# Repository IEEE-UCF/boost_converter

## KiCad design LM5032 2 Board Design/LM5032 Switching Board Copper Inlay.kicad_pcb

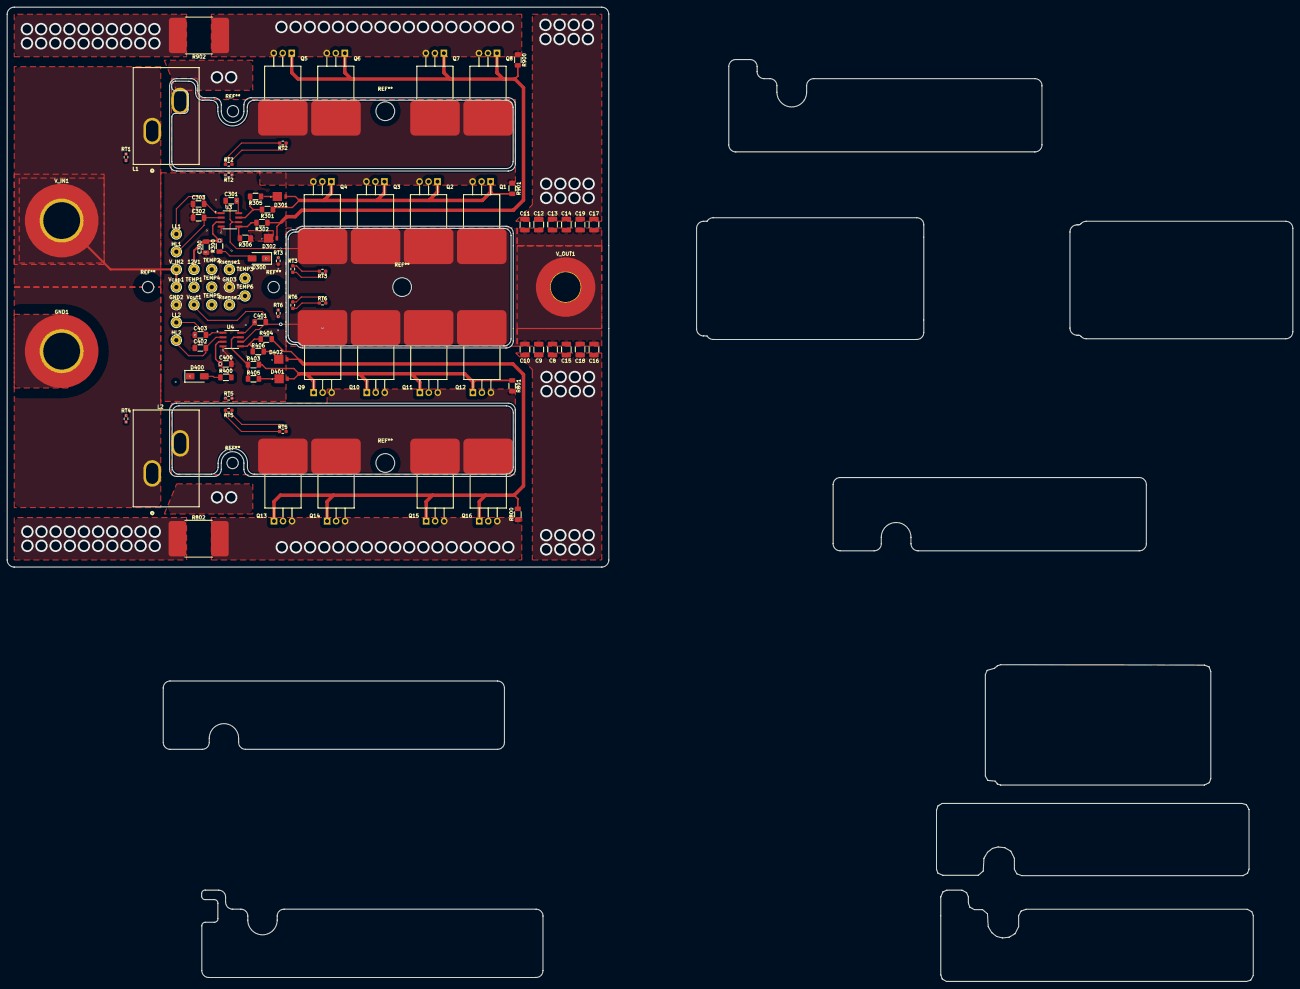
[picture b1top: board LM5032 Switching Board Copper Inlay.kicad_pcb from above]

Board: 4 copper layers, 170.0 x 158.2 mm, 97 parts (0 on the bottom side), 34 nets.

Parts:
12V1: MountingHole_Pad; TestPoint_THTPad_D2.5mm_Drill1.2mm
C8, C9, C10, C11, C12, C13, C14, C15: 10uF; C_1210_3225Metric_Pad1.33x2.70mm_HandSolder
C16, C17, C18, C19: 0.1uF; C_1210_3225Metric_Pad1.33x2.70mm_HandSolder
C300, C400: 22uF; C_1206_3216Metric_Pad1.33x1.80mm_HandSolder
C301, C401: 2.2uF; C_1206_3216Metric_Pad1.33x1.80mm_HandSolder
C302, C303, C402, C403: 33pF; C_1206_3216Metric_Pad1.33x1.80mm_HandSolder
D300, D400: BYG20J-E3/TR; D_SMA
D301, D302, D401, D402: MBRM130LT1G
GND1: MountingHole_Pad; MountingHole_8.4mm_M8_Pad_TopBottom
GND2, GND3: MountingHole_Pad; TestPoint_THTPad_D2.5mm_Drill1.2mm
HL1, HL2: MountingHole_Pad; TestPoint_THTPad_D2.5mm_Drill1.2mm
L1, L2: 470nH; EDITED-IND_IHDM1107BBEVR47M20_VIS
LL1, LL2: MountingHole_Pad; TestPoint_THTPad_D2.5mm_Drill1.2mm
Q1, Q2, Q3, Q4, Q5, Q6, Q7, Q8, Q9, Q10, Q11, Q12, Q13, Q14, Q15, Q16: NMOS; TO-220-3_Horizontal_TabDown no hole
R300, R400: 49.9; R_1206_3216Metric_Pad1.30x1.75mm_HandSolder
R301, R302, R403, R404: 3.3; R_1206_3216Metric_Pad1.30x1.75mm_HandSolder
R305, R306, R405, R406: 2.2; R_1206_3216Metric_Pad1.30x1.75mm_HandSolder
R800, R801, R900, R901: 1k; R_1206_3216Metric_Pad1.30x1.75mm_HandSolder
R802, R902: 0.0001; PSR500HTQFB0L10
RT1, RT2, RT2#2, RT2#3, RT3, RT3#2, RT3#3, RT4, RT5, RT5#2, RT5#3, RT6, RT6#2, RT6#3: 36.5k; R_0603_1608Metric_Pad0.98x0.95mm_HandSolder
Rsense1, Rsense2: MountingHole_Pad; TestPoint_THTPad_D2.5mm_Drill1.2mm
TEMP1, TEMP2, TEMP3, TEMP4, TEMP5, TEMP6: MountingHole_Pad; TestPoint_THTPad_D2.5mm_Drill1.2mm
U3, U4: UCC27712DR; SOIC127P599X175-8N
V_IN1: MountingHole_Pad; MountingHole_8.4mm_M8_Pad_TopBottom
V_IN2: MountingHole_Pad; TestPoint_THTPad_D2.5mm_Drill1.2mm
V_OUT1: MountingHole_Pad; MountingHole_8.4mm_M8_Pad_TopBottom
Vcap1: MountingHole_Pad; TestPoint_THTPad_D2.5mm_Drill1.2mm
Vout1: MountingHole_Pad; TestPoint_THTPad_D2.5mm_Drill1.2mm

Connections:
/12V: 12V1.1, C300.2, C400.2, R300.2, R400.2, U3.3 (VDD), U4.3 (VDD)
/HL1: C302.2, HL1.1, U3.2 (HL)
/HL2: C402.2, HL2.1, U4.2 (HL)
/HO1: D301.2 (A), Q1.2 (G), Q2.2 (G), Q3.2 (G), Q4.2 (G), R301.1, R901.2
/HO2: D401.2 (A), Q9.2 (G), Q10.2 (G), Q11.2 (G), Q12.2 (G), R403.1, R801.2
/LL1: C303.2, LL1.1, U3.1 (LL)
/LL2: C403.2, LL2.1, U4.1 (LL)
/LO1: D302.2 (A), Q5.2 (G), Q6.2 (G), Q7.2 (G), Q8.2 (G), R302.1, R900.2
/LO2: D402.2 (A), Q13.2 (G), Q14.2 (G), Q15.2 (G), Q16.2 (G), R404.1, R800.2
/Rsense1: Q5.3 (S), Q6.3 (S), Q7.3 (S), Q8.3 (S), R900.1, R902.1, Rsense1.1
/Rsense2: Q13.3 (S), Q14.3 (S), Q15.3 (S), Q16.3 (S), R800.1, R802.1, Rsense2.1
GND: C8.2, C9.2, C10.2, C11.2, C12.2, C13.2, C14.2, C15.2, C16.2, C17.2, C18.2, C19.2, C300.1, C302.1, C303.1, C400.1, C402.1, C403.1, GND1.1, GND2.1, GND3.1, R802.2, R902.2, RT1.1, RT2#3.1, RT3#2.2, RT4.2, RT5#3.2, RT6#2.2, U3.4 (COM), U4.4 (COM)
unnamed: D300.2 (A), R300.1
unnamed: C301.1, D300.1 (K), U3.8 (HB)
unnamed: D301.1 (K), R305.1
unnamed: D302.1 (K), R306.1
unnamed: D400.2 (A), R400.1
unnamed: C401.1, D400.1 (K), U4.8 (HB)
unnamed: D401.1 (K), R405.1
unnamed: D402.1 (K), R406.1
unnamed: L1.2, Q1.3 (S), Q2.3 (S), Q3.3 (S), Q4.3 (S), Q5.1 (D), Q6.1 (D), Q7.1 (D), Q8.1 (D), R901.1
unnamed: L2.2, Q9.3 (S), Q10.3 (S), Q11.3 (S), Q12.3 (S), Q13.1 (D), Q14.1 (D), Q15.1 (D), Q16.1 (D), R801.1
unnamed: RT1.2, TEMP1.1
unnamed: RT2#3.2, TEMP2.1
unnamed: RT3#2.1, TEMP3.1
unnamed: RT4.1, TEMP4.1
unnamed: RT5#3.1, TEMP5.1
unnamed: RT6#2.1, TEMP6.1
unnamed: R301.2, R305.2, U3.7 (HO)
unnamed: R302.2, R306.2, U3.5 (LO)
unnamed: R403.2, R405.2, U4.7 (HO)
unnamed: R404.2, R406.2, U4.5 (LO)
Vin: L1.1, L2.1, V_IN1.1, V_IN2.1, Vcap1.1
Vout: C8.1, C9.1, C10.1, C11.1, C12.1, C13.1, C14.1, C15.1, C16.1, C17.1, C18.1, C19.1, C301.2, C401.2, Q1.1 (D), Q2.1 (D), Q3.1 (D), Q4.1 (D), Q9.1 (D), Q10.1 (D), Q11.1 (D), Q12.1 (D), U3.6 (HS), U4.6 (HS), V_OUT1.1, Vout1.1

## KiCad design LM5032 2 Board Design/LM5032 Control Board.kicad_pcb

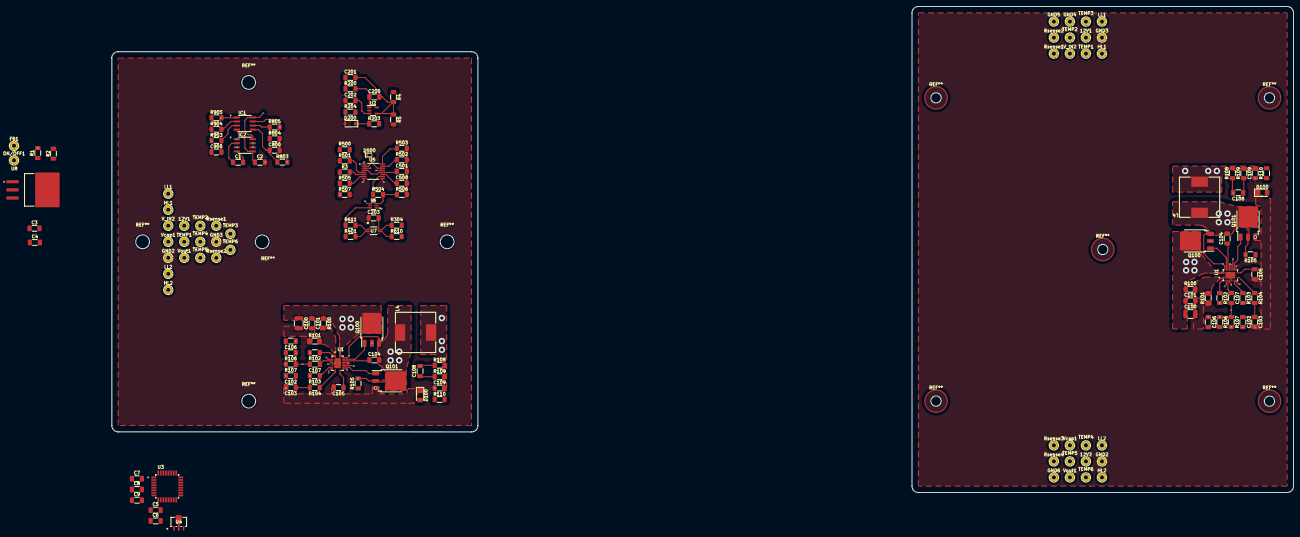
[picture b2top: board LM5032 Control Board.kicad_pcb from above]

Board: 4 copper layers, 368.6 x 151.6 mm, 150 parts (0 on the bottom side), 60 nets.

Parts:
12V1, 12V1#2, 12V2: MountingHole_Pad; TestPoint_THTPad_D2.5mm_Drill1.2mm
C1, C2, C4, C5: 1uF; C_1206_3216Metric_Pad1.33x1.80mm_HandSolder
C3: 4.7uF; C_1206_3216Metric_Pad1.33x1.80mm_HandSolder
C6: 10uF; C_1206_3216Metric_Pad1.33x1.80mm_HandSolder
C7, C8, C9, C201, C202, C203, C500, C501: 0.1uF; C_1206_3216Metric_Pad1.33x1.80mm_HandSolder
C100, C100#2: 10uF; C_1210_3225Metric_Pad1.33x2.70mm_HandSolder
C101, C101#2, C104, C104#2, C105, C105#2: 100nF; C_1206_3216Metric_Pad1.33x1.80mm_HandSolder
C102, C102#2: 56nF; C_1206_3216Metric_Pad1.33x1.80mm_HandSolder
C103, C103#2: 2.2uF; C_1206_3216Metric_Pad1.33x1.80mm_HandSolder
C106, C106#2: 8.2nF; C_1206_3216Metric_Pad1.33x1.80mm_HandSolder
C107, C107#2, C200: 470pF; C_1206_3216Metric_Pad1.33x1.80mm_HandSolder
C108, C108#2: 820pF; C_1206_3216Metric_Pad1.33x1.80mm_HandSolder
C109, C109#2: 22uF; C_1206_3216Metric_Pad1.33x1.80mm_HandSolder
C800, C900: 100pF; C_1206_3216Metric_Pad1.33x1.80mm_HandSolder
D100, D100#2: LED; LED_1206_3216Metric_Pad1.42x1.75mm_HandSolder
D200: 2.0V; D_SOD-123
D500: CMOD4448 TR PBFREE; D_SOD-523
FB1: MountingHole_Pad; TestPoint_THTPad_D2.5mm_Drill1.2mm
GND2, GND2#2, GND3, GND3#2, GND4, GND5, GND6: MountingHole_Pad; TestPoint_THTPad_D2.5mm_Drill1.2mm
HL1, HL1#2, HL2, HL2#2: MountingHole_Pad; TestPoint_THTPad_D2.5mm_Drill1.2mm
IC1: AD8092ARZ; SOIC127P600X175-8N
IC2: MAX1681ESA+; SOIC127P600X175-8N
L4, L4#2: 22uH; IND_MSS1210_COC
LL1, LL1#2, LL2, LL2#2: MountingHole_Pad; TestPoint_THTPad_D2.5mm_Drill1.2mm
ON/OFF1: MountingHole_Pad; TestPoint_THTPad_D2.5mm_Drill1.2mm
Q100, Q100#2, Q101, Q101#2: DMT10H009LK3-13; TO-252-3_TabPin2 modded
R1: 5.36k (47k); R_1206_3216Metric_Pad1.30x1.75mm_HandSolder
R2, R3, R110, R110#2, R610, R611: 1k; R_1206_3216Metric_Pad1.30x1.75mm_HandSolder
R4: 36.5k; R_1206_3216Metric_Pad1.30x1.75mm_HandSolder
R5: 1.37k; R_1206_3216Metric_Pad1.30x1.75mm_HandSolder
R100, R100#2: 62.0k; R_1206_3216Metric_Pad1.30x1.75mm_HandSolder
R101, R101#2: 4.99k; R_1206_3216Metric_Pad1.30x1.75mm_HandSolder
R102, R102#2: 39.2k; R_1206_3216Metric_Pad1.30x1.75mm_HandSolder
R103, R103#2, R104, R104#2: 20k; R_1206_3216Metric_Pad1.30x1.75mm_HandSolder
R105, R105#2: 866; R_1206_3216Metric_Pad1.30x1.75mm_HandSolder
R106, R106#2: 2.87k; R_1206_3216Metric_Pad1.30x1.75mm_HandSolder
R107, R107#2: 1.27k; R_1206_3216Metric_Pad1.30x1.75mm_HandSolder
R108, R108#2: 18k; R_1206_3216Metric_Pad1.30x1.75mm_HandSolder
R109, R109#2: 24.9; R_1206_3216Metric_Pad1.30x1.75mm_HandSolder
R200: 30.1k; R_1206_3216Metric_Pad1.30x1.75mm_HandSolder
R203, R204: 2.0k; R_1206_3216Metric_Pad1.30x1.75mm_HandSolder
R304, R401, R504, R505, R506, R507: 150; R_1206_3216Metric_Pad1.30x1.75mm_HandSolder
R500: 36.5k (35.7k); R_1206_3216Metric_Pad1.30x1.75mm_HandSolder
R501: 1.1k; R_1206_3216Metric_Pad1.30x1.75mm_HandSolder
R502, R503: 34.1k; R_1206_3216Metric_Pad1.30x1.75mm_HandSolder
R803, R903: 300; R_1206_3216Metric_Pad1.30x1.75mm_HandSolder
R804, R904: 10k; R_1206_3216Metric_Pad1.30x1.75mm_HandSolder
R805, R905: 148k; R_1206_3216Metric_Pad1.30x1.75mm_HandSolder
Rsense1, Rsense1#2, Rsense2, Rsense2#2, Rsense3, Rsense4: MountingHole_Pad; TestPoint_THTPad_D2.5mm_Drill1.2mm
TEMP1, TEMP1#2, TEMP2, TEMP2#2, TEMP3, TEMP3#2, TEMP4, TEMP4#2, TEMP5, TEMP5#2, TEMP6, TEMP6#2: MountingHole_Pad; TestPoint_THTPad_D2.5mm_Drill1.2mm
U1, U1#2: LM5146QRGYRQ1; QFN50P450X350X100-21N MODDED
U2: LM8261M5; SOT-23-5
U3: STM32F042K6T6TR; QFP80P900X900X160-32N
U4: MCP1700T-3302E_MB; MCP1700T-3302E_MB updated
U5: LM5032MTCX_NOPB; SOP65P640X120-16N
U6: SN74LVC2G14IDCKRQ1; SOT65P210X110-6N
U7: SN74LVC2G08QDCURQ1; U_VSSOP8_DCU_00_TEX
U8: LM2937ES-5.0; TO254P1524X483-4N modded
V_IN2, V_IN2#2: MountingHole_Pad; TestPoint_THTPad_D2.5mm_Drill1.2mm
Vcap1, Vcap1#2: MountingHole_Pad; TestPoint_THTPad_D2.5mm_Drill1.2mm
Vout1, Vout1#2: MountingHole_Pad; TestPoint_THTPad_D2.5mm_Drill1.2mm

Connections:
/3.3V: C6.2, C7.2, C8.2, C9.2, U3.1 (VDD), U3.5 (VDDA), U3.17 (VDDIO2), U4.3 (VOUT)
/5V: C3.1, C5.2, C203.2, IC1.8 (+VS), IC2.8 (IN), U2.5 (V+), U4.2 (VIN), U6.5 (VCC), U7.8 (VCC), U8.3 (VOUT)
/12V: 12V1.1, 12V1#2.1, C4.2, C109.1, C109#2.1, L4.2, L4#2.2, R108.1, R108#2.1, R109.1, R109#2.1, R110.1, R110#2.1, R203.1, U5.1 (VIN), U8.1 (VIN)
/-5V: C2.2, IC1.4 (-VS), IC2.5 (OUT)
/CS1: IC1.1 (OUT1), R905.1, U5.3 (CS1)
/CS2: IC1.7 (OUT), R805.1, U5.13 (CS2)
/HL1: HL1.1, HL1#2.1, R304.2
/HL2: HL2.1, HL2#2.1, R401.2
/LL1: LL1.1, LL1#2.1, R505.2, R507.1, U6.1 (1A)
/LL2: LL2.1, LL2#2.1, R504.2, R506.1, U6.3 (2A)
/Rsense1: R903.2, Rsense1.1, Rsense2#2.1
/Rsense2: R803.2, Rsense2.1, Rsense4.1
/SS: C501.2, U5.4 (SS1), U5.12 (SS2), U7.1 (1A), U7.5 (2A)
/U5-VCC: R3.2, U5.6 (VCC)
/Vref: C200.2, C201.2, R4.2, R5.1, U2.4 (NEG)
GND: C2.1, C3.2, C4.1, C5.1, C6.1, C7.1, C8.1, C9.1, C100.2, C100#2.2, C101.2, C101#2.2, C103.2, C103#2.2, C105.2, C105#2.2, C109.2, C109#2.2, C202.1, C203.1, C500.1, C501.1, C800.1, C900.1, D100.1 (K), D100#2.1 (K), D200.2 (A), GND2.1, GND2#2.1, GND3.1, GND3#2.1, IC2.1 (FSEL), IC2.3 (GND), IC2.6 (LV), IC2.7 (SHDN), Q101.3 (S), Q101#2.3 (S), R5.2, R101.2, R101#2.2, R107.2, R107#2.2, R501.2, R502.2, R503.2, R506.2, R507.2, R804.2, R904.2, U1.6 (AGND), U1.9 (NC), U1.12 (PGND), U1.15 (EP), U1.16 (NC), U1.21 (EP), U1#2.6 (AGND), U1#2.9 (NC), U1#2.12 (PGND), U1#2.15 (EP), U1#2.16 (NC), U1#2.21 (EP), U2.2 (V-), U3.16 (VSS), U3.32 (VSS), U4.1 (GND), U5.8 (GND1), U5.9 (GND2), U6.2 (GND), U7.4 (GND), U8.2 (GND)
unnamed: C106.1, C106#2.1, R106.2, R106#2.2
unnamed: C108.1, C108#2.1, R109.2, R109#2.2
unnamed: C201.1, R200.2
unnamed: D100.2 (A), D100#2.2 (A), R110.2, R110#2.2
unnamed: D200.1 (K), R203.2, R204.2
unnamed: D500.2 (A), U5.2 (COMP1), U5.14 (COMP2)
unnamed: C200.1, D500.1 (K), R200.1, U2.1 (OUT)
unnamed: FB1.1, R3.1
unnamed: C900.2, IC1.3 (+IN1), R903.1
unnamed: C800.2, IC1.5 (+IN2), R803.1
unnamed: IC1.2 (-IN1), R904.1, R905.2
unnamed: IC1.6 (-IN2), R804.1, R805.2
unnamed: C1.2, IC2.2 (CAP+)
unnamed: C1.1, IC2.4 (CAP-)
unnamed: ON/OFF1.1, R1.1
unnamed: Q100.2 (G), Q100#2.2 (G), U1.18 (HO), U1#2.18 (HO)
unnamed: C104.2, C104#2.2, L4.1, L4#2.1, Q100.3 (S), Q100#2.3 (S), Q101.1 (D), Q101#2.1 (D), R105.1, R105#2.1, U1.19 (SW), U1#2.19 (SW)
unnamed: Q101.2 (G), Q101#2.2 (G), U1.13 (LO), U1#2.13 (LO)
unnamed: R2.1, Vcap1.1
unnamed: C104.1, C104#2.1, U1.17 (BST), U1#2.17 (BST)
unnamed: C106.2, C106#2.2, C107.2, C107#2.2, U1.4 (COMP), U1#2.4 (COMP)
unnamed: R100.2, R100#2.2, R101.1, R101#2.1, U1.1 (EN_UVLO), U1#2.1 (EN_UVLO)
unnamed: C107.1, C107#2.1, C108.2, C108#2.2, R106.1, R106#2.1, R107.1, R107#2.1, R108.2, R108#2.2, U1.5 (FB), U1#2.5 (FB)
unnamed: C105.1, C105#2.1, R105.2, R105#2.2, U1.11 (ILIM), U1#2.11 (ILIM)
unnamed: R104.1, R104#2.1, U1.10 (PGOOD), U1#2.10 (PGOOD)
unnamed: R102.1, R102#2.1, U1.2 (RT), U1#2.2 (RT)
unnamed: C102.1, C102#2.1, U1.3 (SS_TRK), U1#2.3 (SS_TRK)
unnamed: R103.1, R103#2.1, U1.8 (SYNCIN), U1#2.8 (SYNCIN)
unnamed: C102.2, C102#2.2, C103.1, C103#2.1, R102.2, R102#2.2, R103.2, R103#2.2, R104.2, R104#2.2, U1.14 (VCC), U1#2.14 (VCC)
unnamed: C202.2, R204.1, U2.3 (POS)
unnamed: R502.1, U5.15 (DCL)
unnamed: R505.1, U5.7 (OUT1)
unnamed: R504.1, U5.10 (OUT2)
unnamed: C500.2, U5.11 (RES)
unnamed: R503.1, U5.16 (RT/SYNC)
unnamed: R1.2, R500.2, R501.1, U5.5 (UVLO)
unnamed: R611.1, U6.6 (1Y)
unnamed: R610.1, U6.4 (2Y)
unnamed: R611.2, U7.2 (1B)
unnamed: R304.1, U7.7 (1Y)
unnamed: R610.2, U7.6 (2B)
unnamed: R401.1, U7.3 (2Y)
Vin: C100.1, C100#2.1, C101.1, C101#2.1, Q100.1 (D), Q100#2.1 (D), R2.2, R100.1, R100#2.1, R500.1, U1.20 (VIN), U1#2.20 (VIN), V_IN2.1, V_IN2#2.1, Vcap1#2.1
Vout: R4.1, Vout1.1, Vout1#2.1

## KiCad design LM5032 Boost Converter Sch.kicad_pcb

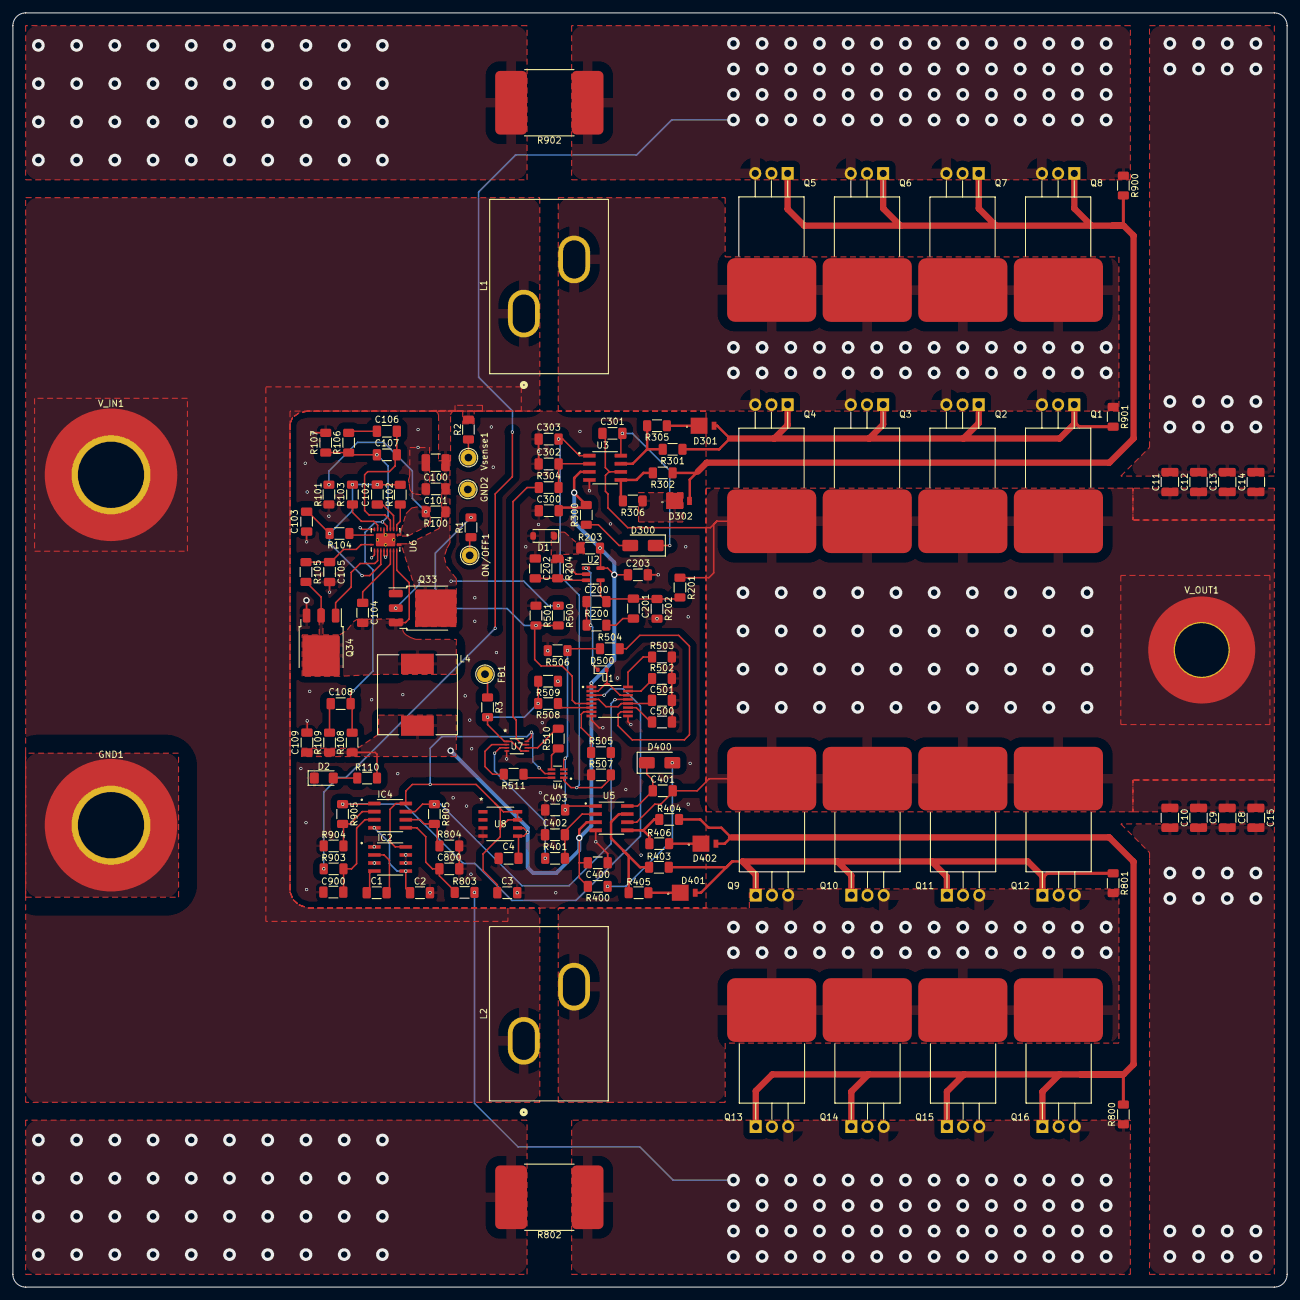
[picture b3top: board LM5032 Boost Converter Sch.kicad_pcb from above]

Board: 2 copper layers, 200.0 x 200.0 mm, 140 parts (0 on the bottom side), 78 nets.

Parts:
C1, C2, C4: 1uF; C_1206_3216Metric_Pad1.33x1.80mm_HandSolder
C3: 4.7uF; C_1206_3216Metric_Pad1.33x1.80mm_HandSolder
C8, C9, C10, C11, C12, C13, C14, C15, C100: 10uF; C_1210_3225Metric_Pad1.33x2.70mm_HandSolder
C101, C104, C105: 100nF; C_1206_3216Metric_Pad1.33x1.80mm_HandSolder
C102: 56nF; C_1206_3216Metric_Pad1.33x1.80mm_HandSolder
C103, C301, C401: 2.2uF; C_1206_3216Metric_Pad1.33x1.80mm_HandSolder
C106: 8.2nF; C_1206_3216Metric_Pad1.33x1.80mm_HandSolder
C107, C200: 470pF; C_1206_3216Metric_Pad1.33x1.80mm_HandSolder
C108: 820pF; C_1206_3216Metric_Pad1.33x1.80mm_HandSolder
C109, C300, C400: 22uF; C_1206_3216Metric_Pad1.33x1.80mm_HandSolder
C201, C202, C203, C500, C501: 0.1uF; C_1206_3216Metric_Pad1.33x1.80mm_HandSolder
C302, C303, C402, C403: 33pF; C_1206_3216Metric_Pad1.33x1.80mm_HandSolder
C800, C900: 100pF; C_1206_3216Metric_Pad1.33x1.80mm_HandSolder
D1: 2.0V; D_SOD-123
D2: LED; LED_1206_3216Metric_Pad1.42x1.75mm_HandSolder
D300, D400: BYG20J-E3/TR; D_SMA
D301, D302, D401, D402: MBRM130LT1G
D500: CMOD4448 TR PBFREE; D_SOD-523
FB1: MountingHole_Pad; TestPoint_THTPad_D2.5mm_Drill1.2mm
GND1: MountingHole_Pad; MountingHole_8.4mm_M8_Pad_TopBottom
GND2: MountingHole_Pad; TestPoint_THTPad_D2.5mm_Drill1.2mm
IC2: MAX1681ESA+; SOIC127P600X175-8N
IC4: AD8092ARZ; SOIC127P600X175-8N
L1, L2: 470nH; EDITED-IND_IHDM1107BBEVR47M20_VIS
L4: 22uH; IND_MSS1210_COC
ON/OFF1: MountingHole_Pad; TestPoint_THTPad_D2.5mm_Drill1.2mm
Q1, Q2, Q3, Q4, Q5, Q6, Q7, Q8, Q9, Q10, Q11, Q12, Q13, Q14, Q15, Q16: NMOS; TO-220-3_Horizontal_TabDown no hole
Q33, Q34: DMT10H009LK3-13; TO-252-3_TabPin2 modded
R1: 47k; R_1206_3216Metric_Pad1.30x1.75mm_HandSolder
R2, R110, R510, R511, R800, R801, R900, R901: 1k; R_1206_3216Metric_Pad1.30x1.75mm_HandSolder
R3, R804, R904: 10k; R_1206_3216Metric_Pad1.30x1.75mm_HandSolder
R100: 62.0k; R_1206_3216Metric_Pad1.30x1.75mm_HandSolder
R101: 4.99k; R_1206_3216Metric_Pad1.30x1.75mm_HandSolder
R102: 39.2k; R_1206_3216Metric_Pad1.30x1.75mm_HandSolder
R103, R104: 20k; R_1206_3216Metric_Pad1.30x1.75mm_HandSolder
R105: 866; R_1206_3216Metric_Pad1.30x1.75mm_HandSolder
R106: 2.87k; R_1206_3216Metric_Pad1.30x1.75mm_HandSolder
R107: 1.27k; R_1206_3216Metric_Pad1.30x1.75mm_HandSolder
R108: 18k; R_1206_3216Metric_Pad1.30x1.75mm_HandSolder
R109: 24.9; R_1206_3216Metric_Pad1.30x1.75mm_HandSolder
R200: 30.1k; R_1206_3216Metric_Pad1.30x1.75mm_HandSolder
R201: 36.5k; R_1206_3216Metric_Pad1.30x1.75mm_HandSolder
R202: 1.37k; R_1206_3216Metric_Pad1.30x1.75mm_HandSolder
R203, R204: 2.0k; R_1206_3216Metric_Pad1.30x1.75mm_HandSolder
R300, R400: 49.9; R_1206_3216Metric_Pad1.30x1.75mm_HandSolder
R301, R302, R403, R404: 3.3; R_1206_3216Metric_Pad1.30x1.75mm_HandSolder
R304, R401, R504, R505, R506, R507, R508, R509: 150; R_1206_3216Metric_Pad1.30x1.75mm_HandSolder
R305, R306, R405, R406: 2.2; R_1206_3216Metric_Pad1.30x1.75mm_HandSolder
R500: 35.7k; R_1206_3216Metric_Pad1.30x1.75mm_HandSolder
R501: 1.1k; R_1206_3216Metric_Pad1.30x1.75mm_HandSolder
R502: 28.7k; R_1206_3216Metric_Pad1.30x1.75mm_HandSolder
R503: 34.1k; R_1206_3216Metric_Pad1.30x1.75mm_HandSolder
R802, R902: 0.0001; PSR500HTQFB0L10
R803, R903: 300; R_1206_3216Metric_Pad1.30x1.75mm_HandSolder
R805, R905: 148k; R_1206_3216Metric_Pad1.30x1.75mm_HandSolder
U1: LM5032MTCX_NOPB; SOP65P640X120-16N
U2: LM8261M5; SOT-23-5
U3, U5: UCC27712DR; SOIC127P599X175-8N
U4: SN74LVC2G14IDCKRQ1; SOT65P210X110-6N
U6: LM5146QRGYRQ1; QFN50P450X350X100-21N MODDED
U7: SN74LVC2G08QDCURQ1; U_VSSOP8_DCU_00_TEX
U8: TPS76650DRM3; D8
V_IN1: MountingHole_Pad; MountingHole_8.4mm_M8_Pad_TopBottom
V_OUT1: MountingHole_Pad; MountingHole_8.4mm_M8_Pad_TopBottom
Vsense1: MountingHole_Pad; TestPoint_THTPad_D2.5mm_Drill1.2mm

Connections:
/5V: C3.1, IC2.8 (IN), IC4.8 (+VS), U4.5 (VCC), U7.8 (VCC), U8.7 (OUT), U8.8 (OUT)
/12V: C4.2, C109.1, C203.2, C300.2, C400.2, L4.2, R108.1, R109.1, R110.1, R203.1, R300.2, R400.2, U1.1 (VIN), U2.5 (V+), U3.3 (VDD), U5.3 (VDD), U8.5 (IN), U8.6 (IN)
/-5V: C2.2, IC2.5 (OUT), IC4.4 (-VS)
/CS1: IC4.1 (OUT1), R905.1, U1.3 (CS1)
/CS2: IC4.7 (OUT), R805.1, U1.13 (CS2)
/HO1: D301.2 (A), Q1.2 (G), Q2.2 (G), Q3.2 (G), Q4.2 (G), R301.1, R901.2
/HO2: D401.2 (A), Q9.2 (G), Q10.2 (G), Q11.2 (G), Q12.2 (G), R403.1, R801.2
/LO1: D302.2 (A), Q5.2 (G), Q6.2 (G), Q7.2 (G), Q8.2 (G), R302.1, R900.2
/LO2: D402.2 (A), Q13.2 (G), Q14.2 (G), Q15.2 (G), Q16.2 (G), R404.1, R800.2
/U1-VCC: R3.2, R508.1, R509.2, U7.1 (1A), U7.5 (2A)
GND: C2.1, C3.2, C4.1, C8.2, C9.2, C10.2, C11.2, C12.2, C13.2, C14.2, C15.2, C100.2, C101.2, C103.2, C105.2, C109.2, C202.1, C203.1, C300.1, C302.1, C303.1, C400.1, C402.1, C403.1, C500.1, C501.1, C800.1, C900.1, D1.2 (A), D2.1 (K), GND1.1, GND2.1, IC2.1 (FSEL), IC2.3 (GND), IC2.6 (LV), IC2.7 (SHDN), Q34.3 (S), R101.2, R107.2, R202.2, R501.2, R502.2, R503.2, R506.2, R507.2, R509.1, R802.2, R804.2, R902.2, R904.2, U1.8 (GND1), U1.9 (GND2), U2.2 (V-), U3.4 (COM), U4.2 (GND), U5.4 (COM), U6.6 (AGND), U6.9 (NC), U6.12 (PGND), U6.15 (EP), U6.16 (NC), U6.21 (EP), U7.4 (GND), U8.3 (GND), U8.4 (*EN)
unnamed: C106.1, R106.2
unnamed: C108.1, R109.2
unnamed: C201.1, R200.2
unnamed: D1.1 (K), R203.2, R204.2
unnamed: D2.2 (A), R110.2
unnamed: D300.2 (A), R300.1
unnamed: C301.1, D300.1 (K), U3.8 (HB)
unnamed: D301.1 (K), R305.1
unnamed: D302.1 (K), R306.1
unnamed: D400.2 (A), R400.1
unnamed: C401.1, D400.1 (K), U5.8 (HB)
unnamed: D401.1 (K), R405.1
unnamed: D402.1 (K), R406.1
unnamed: D500.2 (A), U1.2 (COMP1), U1.14 (COMP2)
unnamed: C200.1, D500.1 (K), R200.1, U2.1 (OUT)
unnamed: FB1.1, R3.1
unnamed: C1.2, IC2.2 (CAP+)
unnamed: C1.1, IC2.4 (CAP-)
unnamed: C900.2, IC4.3 (+IN1), R903.1
unnamed: C800.2, IC4.5 (+IN2), R803.1
unnamed: IC4.2 (-IN1), R904.1, R905.2
unnamed: IC4.6 (-IN2), R804.1, R805.2
unnamed: ON/OFF1.1, R1.1
unnamed: L1.2, Q1.3 (S), Q2.3 (S), Q3.3 (S), Q4.3 (S), Q5.1 (D), Q6.1 (D), Q7.1 (D), Q8.1 (D), R901.1
unnamed: Q5.3 (S), Q6.3 (S), Q7.3 (S), Q8.3 (S), R900.1, R902.1, R903.2
unnamed: L2.2, Q9.3 (S), Q10.3 (S), Q11.3 (S), Q12.3 (S), Q13.1 (D), Q14.1 (D), Q15.1 (D), Q16.1 (D), R801.1
unnamed: Q13.3 (S), Q14.3 (S), Q15.3 (S), Q16.3 (S), R800.1, R802.1, R803.2
unnamed: Q33.2 (G), U6.18 (HO)
unnamed: C104.2, L4.1, Q33.3 (S), Q34.1 (D), R105.1, U6.19 (SW)
unnamed: Q34.2 (G), U6.13 (LO)
unnamed: R2.1, Vsense1.1
unnamed: R502.1, U1.15 (DCL)
unnamed: R505.1, U1.7 (OUT1)
unnamed: R504.1, U1.10 (OUT2)
unnamed: C500.2, U1.11 (RES)
unnamed: R503.1, U1.16 (RT/SYNC)
unnamed: C501.2, U1.4 (SS1), U1.12 (SS2)
unnamed: R1.2, R500.2, R501.1, U1.5 (UVLO)
unnamed: R508.2, U1.6 (VCC)
unnamed: C200.2, C201.2, R201.2, R202.1, U2.4 (NEG)
unnamed: C202.2, R204.1, U2.3 (POS)
unnamed: C302.2, R304.2, U3.2 (HL)
unnamed: R301.2, R305.2, U3.7 (HO)
unnamed: C303.2, R505.2, R507.1, U3.1 (LL), U4.1 (1A)
unnamed: R302.2, R306.2, U3.5 (LO)
unnamed: R511.1, U4.6 (1Y)
unnamed: C403.2, R504.2, R506.1, U4.3 (2A), U5.1 (LL)
unnamed: R510.1, U4.4 (2Y)
unnamed: C402.2, R401.2, U5.2 (HL)
unnamed: R403.2, R405.2, U5.7 (HO)
unnamed: R404.2, R406.2, U5.5 (LO)
unnamed: C104.1, U6.17 (BST)
unnamed: C106.2, C107.2, U6.4 (COMP)
unnamed: R100.2, R101.1, U6.1 (EN_UVLO)
unnamed: C107.1, C108.2, R106.1, R107.1, R108.2, U6.5 (FB)
unnamed: C105.1, R105.2, U6.11 (ILIM)
unnamed: R104.1, U6.10 (PGOOD)
unnamed: R102.1, U6.2 (RT)
unnamed: C102.1, U6.3 (SS_TRK)
unnamed: R103.1, U6.8 (SYNCIN)
unnamed: C102.2, C103.1, R102.2, R103.2, R104.2, U6.14 (VCC)
unnamed: R511.2, U7.2 (1B)
unnamed: R304.1, U7.7 (1Y)
unnamed: R510.2, U7.6 (2B)
unnamed: R401.1, U7.3 (2Y)
Vin: C100.1, C101.1, L1.1, L2.1, Q33.1 (D), R2.2, R100.1, R500.1, U6.20 (VIN), V_IN1.1
Vout: C8.1, C9.1, C10.1, C11.1, C12.1, C13.1, C14.1, C15.1, C301.2, C401.2, Q1.1 (D), Q2.1 (D), Q3.1 (D), Q4.1 (D), Q9.1 (D), Q10.1 (D), Q11.1 (D), Q12.1 (D), R201.1, U3.6 (HS), U5.6 (HS), V_OUT1.1

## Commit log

2024-02-29 'update'
